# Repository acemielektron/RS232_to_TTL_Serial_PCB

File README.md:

# RS232_to_TTL_Serial_PCB
diy pcb for Sparkfun's discontinued rs232 to ttl serial hack adapter 

RS232 shifter (https://www.sparkfun.com/products/retired/133)

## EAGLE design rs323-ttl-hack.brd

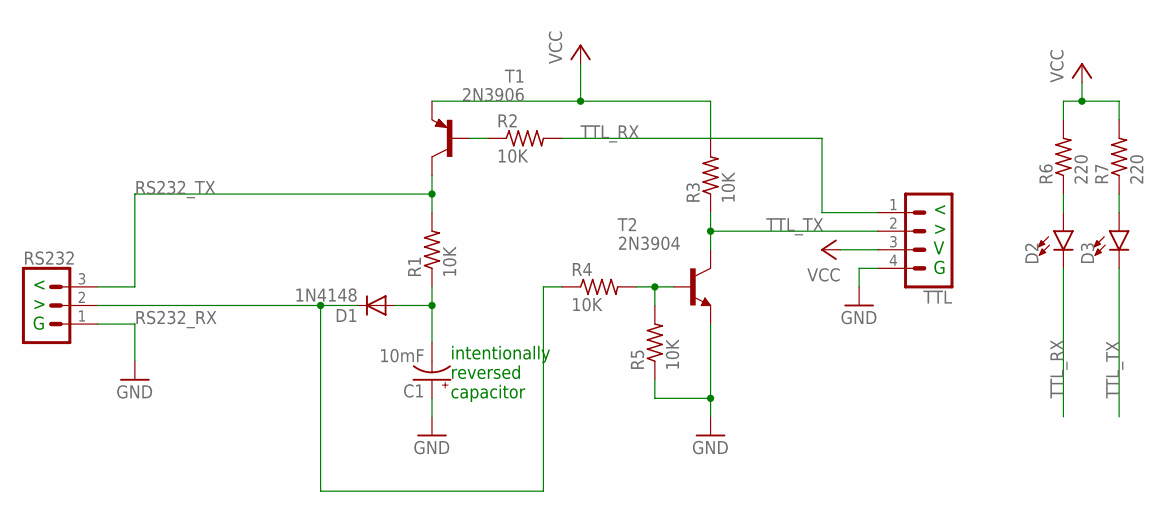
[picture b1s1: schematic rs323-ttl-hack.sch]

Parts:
C1: 10mF; E2,5-6
D1: 1N4148; DO35-10
D2, D3: LED3MM; LED_3MM
R1, R2, R3, R4, R5: 10K; 0207/10
R6, R7: 220; 0207/10
RS232: CONN_03; 1X03
T1: 2N3906; TO92-EBC
T2: 2N3904; TO92-EBC
TTL: CONN_04; 1X04

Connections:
GND: C1.+, R5.1, RS232.1, T2.E, TTL.4
unnamed: R2.1, T1.B
unnamed: C1.-, D1.A, R1.1
unnamed: D2.A, R6.1
unnamed: R4.2, R5.2, T2.B
unnamed: D3.A, R7.1
RS232_RX: D1.C, R4.1, RS232.2
RS232_TX: R1.2, RS232.3, T1.C
TTL_RX: D2.K (C), R2.2, TTL.1
TTL_TX: D3.K (C), R3.1, T2.C, TTL.2
VCC: R3.2, R6.2, R7.2, T1.E, TTL.3

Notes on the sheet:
intentionally reversed capacitor
< > G
< > V G

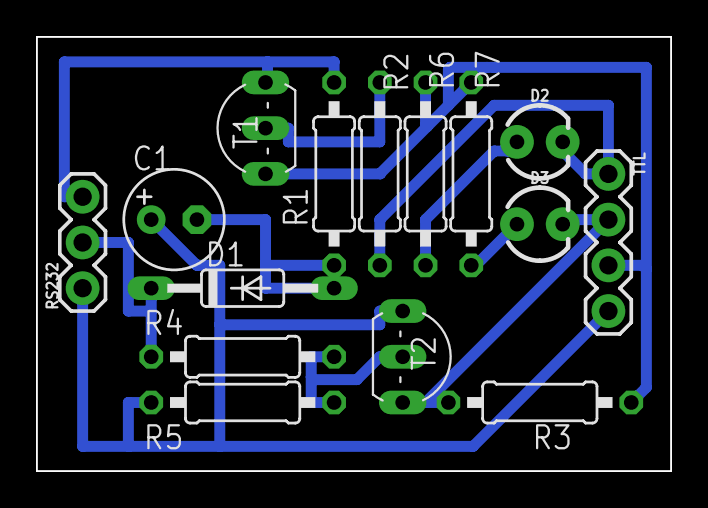
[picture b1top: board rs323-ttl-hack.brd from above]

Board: 2 copper layers, 35.2 x 24.1 mm, 15 parts (0 on the bottom side), 11 nets.

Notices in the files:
parts and their libraries:
SparkFun-Connectors: Licensing: Creative Commons ShareAlike 4.0 International - https://creativecommons.org/licenses/by-sa/4.0
